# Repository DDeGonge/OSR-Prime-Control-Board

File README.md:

# OSR-Prime-Control-Board
It's like the OSR but more power more better

This repo is being deprecated. The board and arduino packages have been merged into the [OSR repo](https://github.com/DDeGonge/OSR-Control-Board)

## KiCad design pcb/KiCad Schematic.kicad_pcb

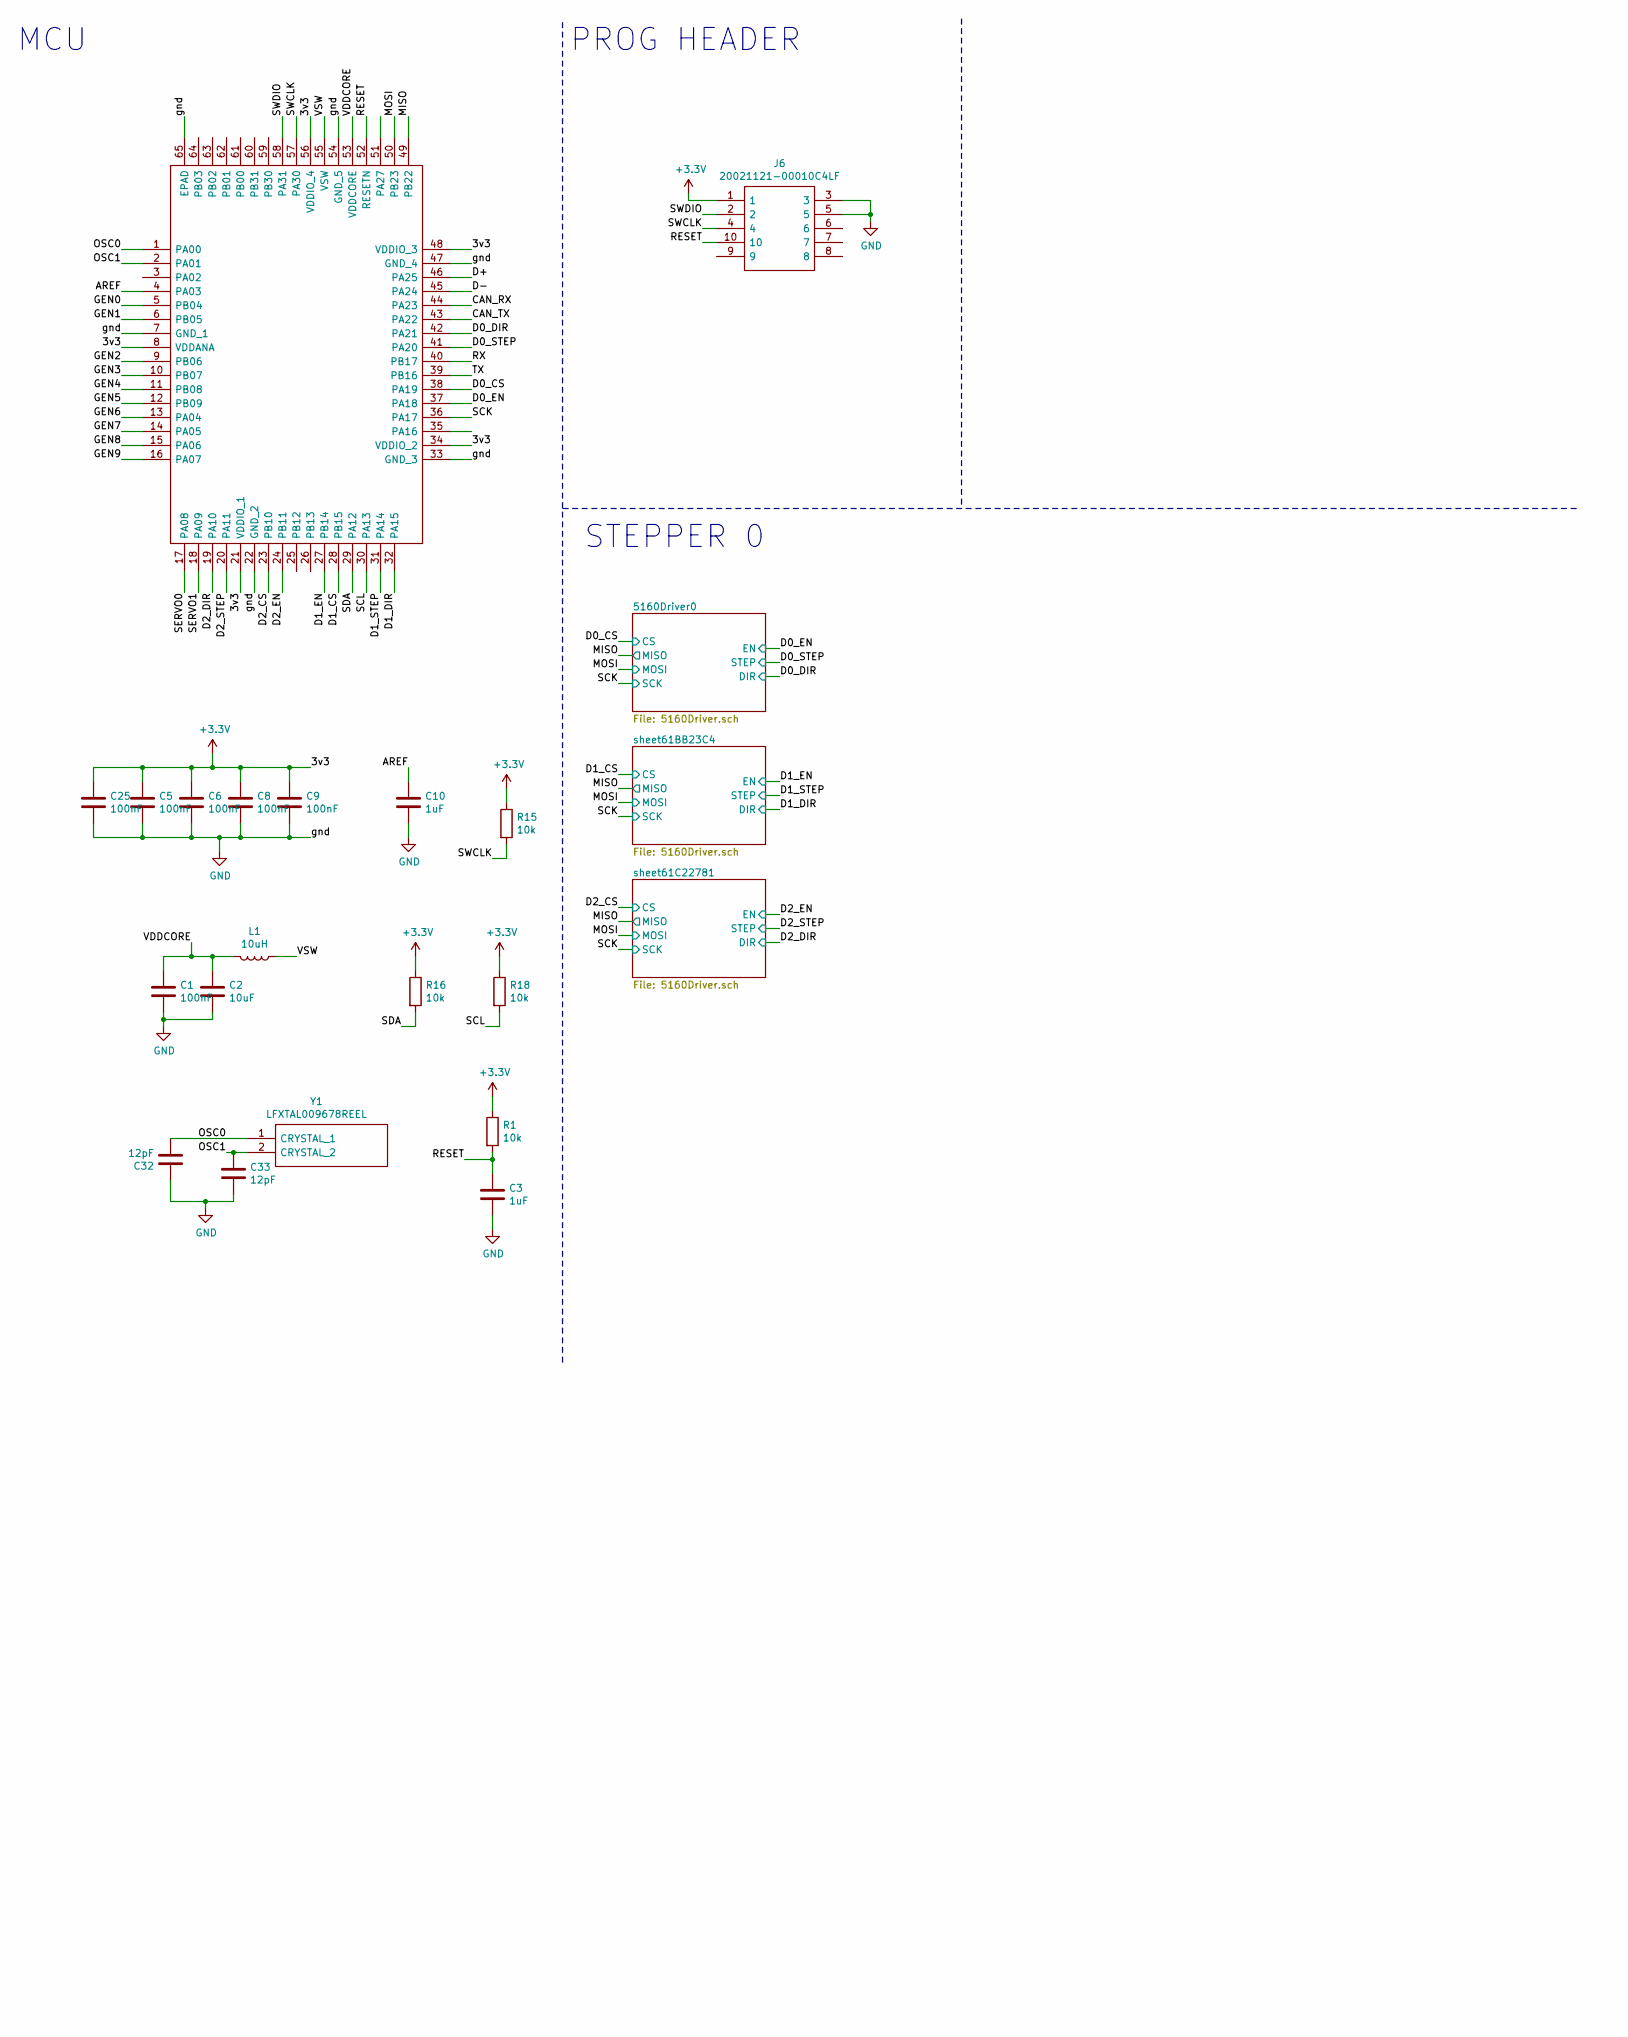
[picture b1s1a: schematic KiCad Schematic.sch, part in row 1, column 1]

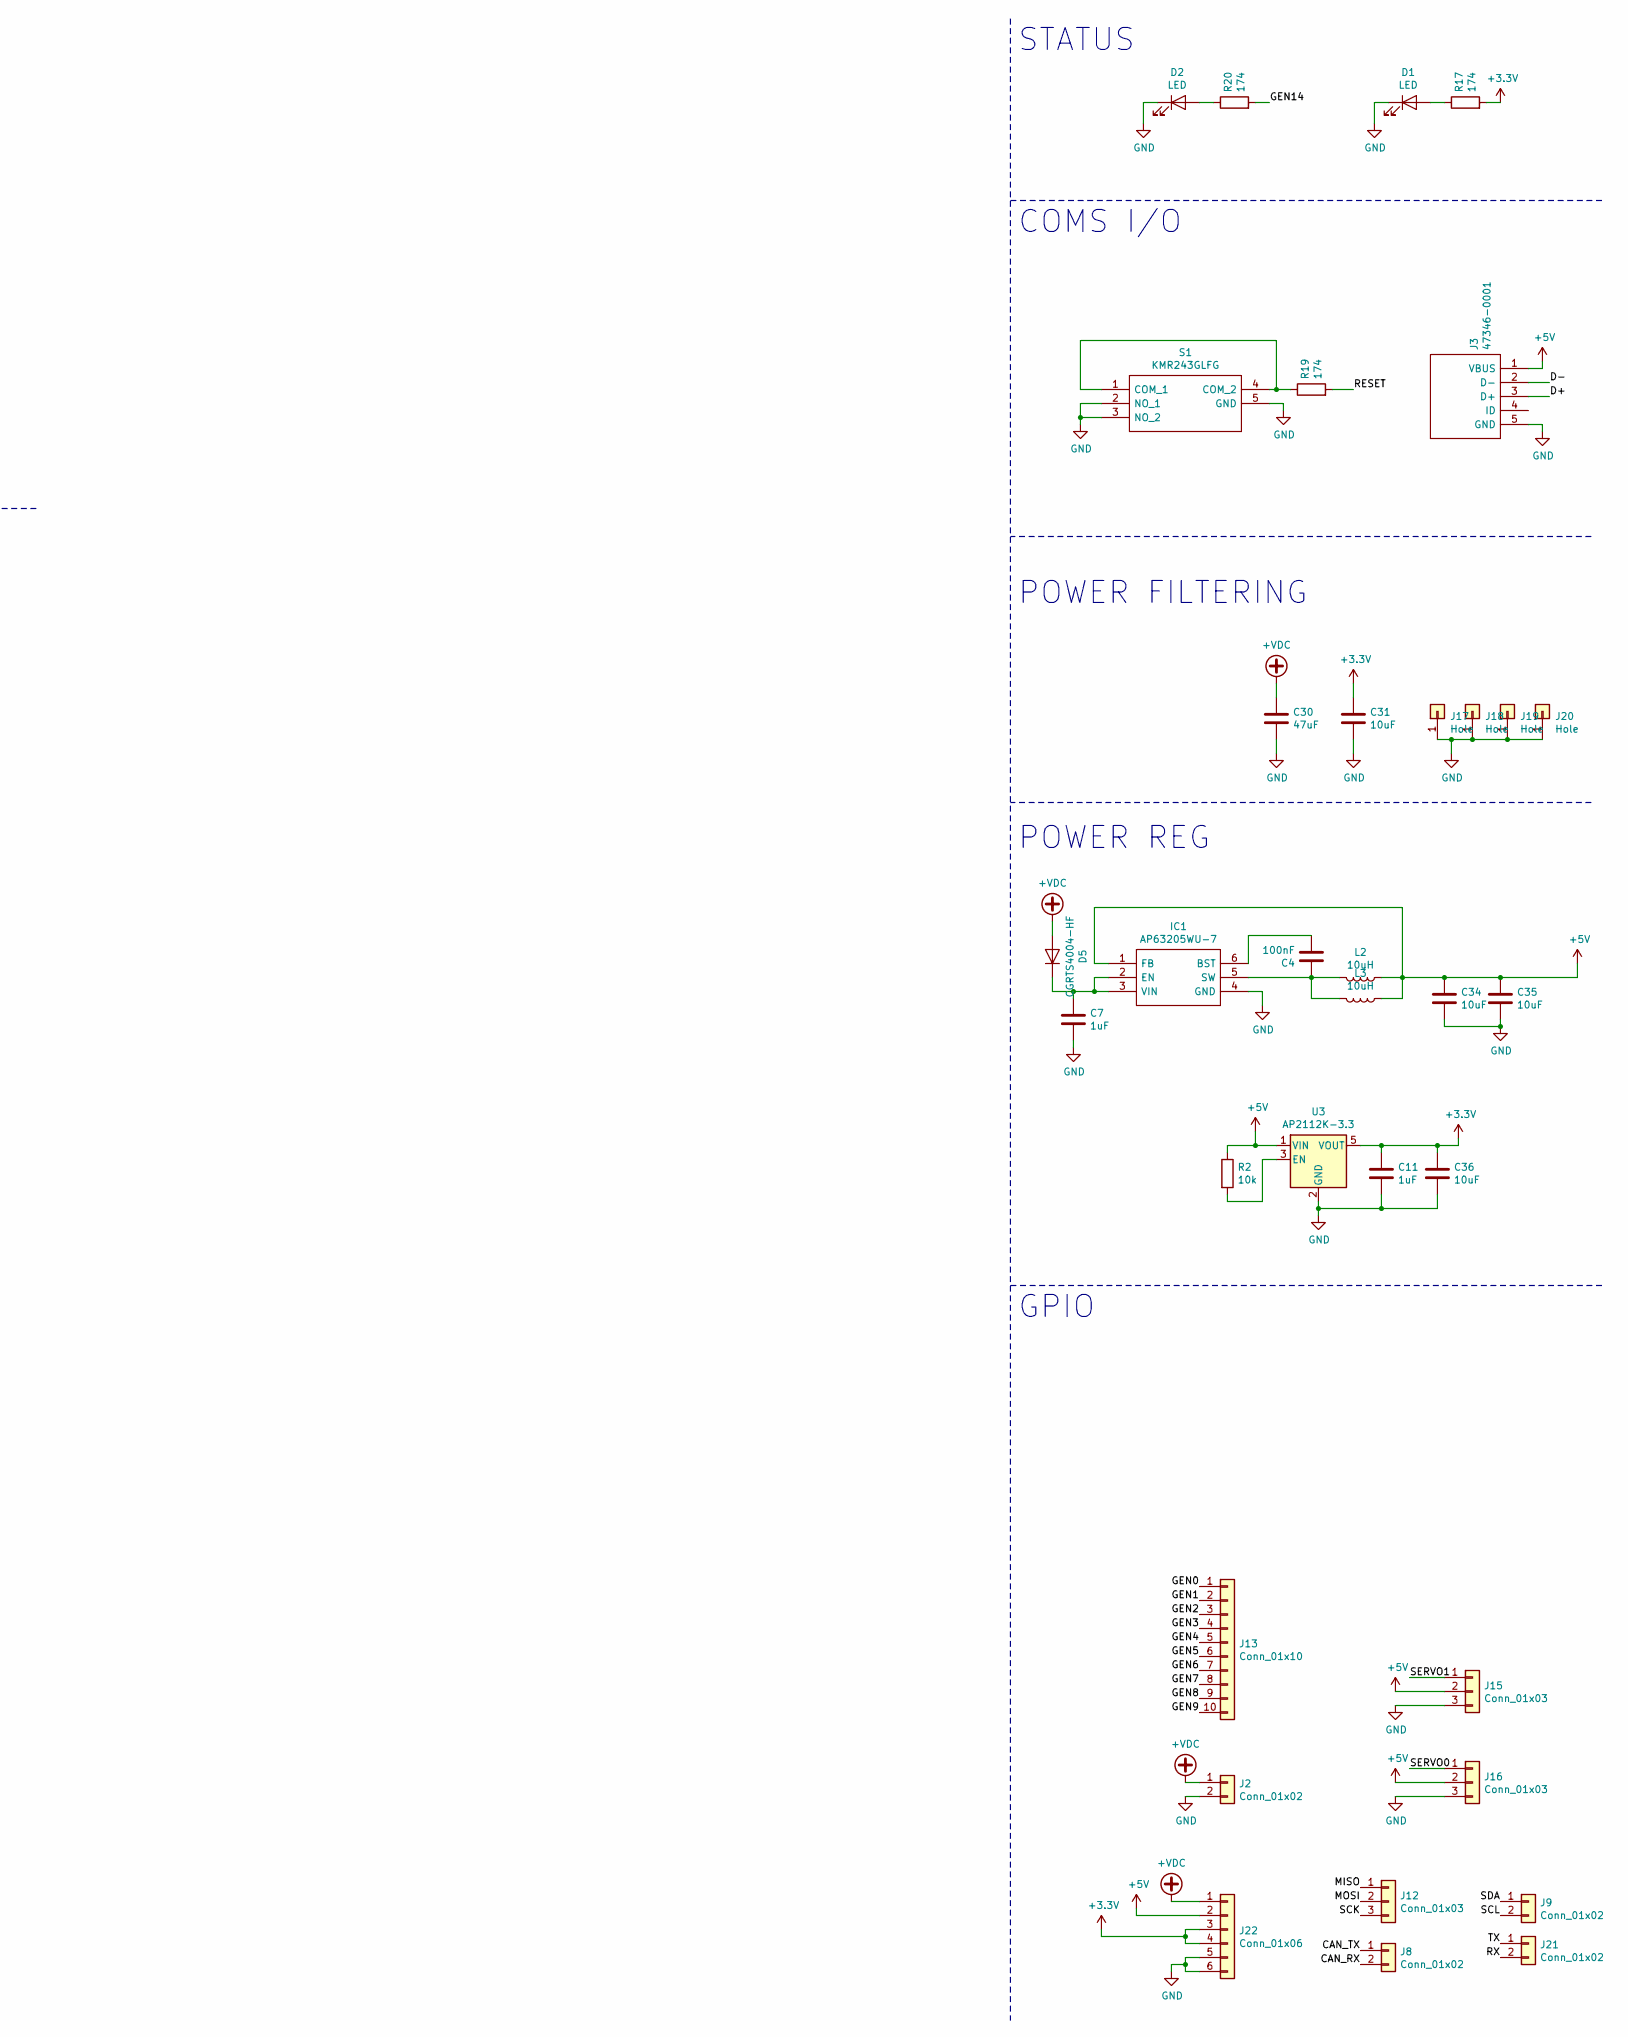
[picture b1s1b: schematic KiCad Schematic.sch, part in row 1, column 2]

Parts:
C1, C4, C5, C6, C8, C9, C25: 100nF; C_0603_1608Metric
C2, C31, C34, C35, C36: 10uF; C_0805_2012Metric
C3, C7, C10, C11: 1uF; C_0603_1608Metric
C30: 47uF; CP_Elec_6.3x7.7
C32, C33: 12pF; C_0603_1608Metric
D1, D2: LED; LED_0603_1608Metric
D5: CGRTS4004-HF; D_SOD-123F
IC1: AP63205WU-7; SOT95P280X100-6N; Mouser Part Number 621-AP63205WU-7
IC2: ATSAMD51J19A-MU; QFN-64-1EP_9x9mm_P0.5mm_EP6x6mm_ThermalVias; Mouser Part Number 556-ATSAMD51J19AMU
J2: Conn_01x02; BarrelJack_Wuerth_6941xx301002
J3: 47346-0001; Mouser Part Number 538-47346-0001
J6: 20021121-00010C4LF; 2002112100010C4LF; Mouser Part Number 649-202112100010C4LF
J8, J9, J21: Conn_01x02; PinHeader_1x02_P2.54mm_Vertical
J12, J15, J16: Conn_01x03; PinHeader_1x03_P2.54mm_Vertical
J13: Conn_01x10; PinHeader_1x10_P2.54mm_Vertical
J17, J18, J19, J20: Hole; MountingHole_2.7mm_M2.5_DIN965_Pad
J22: Conn_01x06; PinSocket_1x06_P2.54mm_Vertical
L1, L2, L3: 10uH; L_0805_2012Metric
R1, R2, R15, R16, R18: 10k; R_0603_1608Metric
R17, R19, R20: 174; R_0603_1608Metric
S1: KMR243GLFG; KMR421GULCLFS; Mouser Part Number 611-KMR243GLFG
U3: AP2112K-3.3; SOT-23-5
Y1: LFXTAL009678REEL; Mouser Part Number 449-LFXTAL009678REEL

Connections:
+3V3: C5.1, C6.1, C8.1, C9.1, C11.1, C25.1, C31.1, C36.1, IC2.8 (VDDANA), IC2.21 (VDDIO_1), IC2.34 (VDDIO_2), IC2.48 (VDDIO_3), IC2.56 (VDDIO_4), J6.1, J22.3, J22.4, R1.1, R15.1, R16.1, R17.2, R18.1, U3.5 (VOUT); also elsewhere on the board
+5V: C34.1, C35.1, IC1.1 (FB), J3.1 (VBUS), J15.2, J16.2, J22.2, L2.1, L3.1, R2.1, U3.1 (VIN); also elsewhere on the board
+VDC: C30.1, D5.2 (A), J2.1, J22.1; also elsewhere on the board
/AREF: C10.1, IC2.4 (PA03)
/CAN_RX: IC2.44 (PA23), J8.2
/CAN_TX: IC2.43 (PA22), J8.1
/D0_CS: IC2.38 (PA19); also elsewhere on the board
/D0_DIR: IC2.42 (PA21); also elsewhere on the board
/D0_EN: IC2.37 (PA18); also elsewhere on the board
/D0_STEP: IC2.41 (PA20); also elsewhere on the board
/D1_CS: IC2.28 (PB15); also elsewhere on the board
/D1_DIR: IC2.32 (PA15); also elsewhere on the board
/D1_EN: IC2.27 (PB14); also elsewhere on the board
/D1_STEP: IC2.31 (PA14); also elsewhere on the board
/D2_CS: IC2.23 (PB10); also elsewhere on the board
/D2_DIR: IC2.19 (PA10); also elsewhere on the board
/D2_EN: IC2.24 (PB11); also elsewhere on the board
/D2_STEP: IC2.20 (PA11); also elsewhere on the board
/D+: IC2.46 (PA25), J3.3 (D+)
/D-: IC2.45 (PA24), J3.2 (D-)
/GEN0: IC2.5 (PB04), J13.1
/GEN1: IC2.6 (PB05), J13.2
/GEN2: IC2.9 (PB06), J13.3
/GEN3: IC2.10 (PB07), J13.4
/GEN4: IC2.11 (PB08), J13.5
/GEN5: IC2.12 (PB09), J13.6
/GEN6: IC2.13 (PA04), J13.7
/GEN7: IC2.14 (PA05), J13.8
/GEN8: IC2.15 (PA06), J13.9
/GEN9: IC2.16 (PA07), J13.10
/GEN14: R20.2
/MISO: IC2.49 (PB22), J12.1; also elsewhere on the board
/MOSI: IC2.50 (PB23), J12.2; also elsewhere on the board
/OSC0: C32.2, IC2.1 (PA00), Y1.1 (CRYSTAL_1)
/OSC1: C33.1, IC2.2 (PA01), Y1.2 (CRYSTAL_2)
/RESET: C3.1, IC2.52 (RESETN), J6.10, R1.2, R19.2
/RX: IC2.40 (PB17), J21.2
/SCK: IC2.36 (PA17), J12.3; also elsewhere on the board
/SCL: IC2.30 (PA13), J9.2, R18.2
/SDA: IC2.29 (PA12), J9.1, R16.2
/SERVO0: IC2.17 (PA08), J16.1
/SERVO1: IC2.18 (PA09), J15.1
/SWCLK: IC2.57 (PA30), J6.4, R15.2
/SWDIO: IC2.58 (PA31), J6.2
/TX: IC2.39 (PB16), J21.1
/VDDCORE: C1.1, C2.1, IC2.53 (VDDCORE), L1.2
/VSW: IC2.55 (VSW), L1.1
GND: C1.2, C2.2, C3.2, C5.2, C6.2, C7.2, C8.2, C9.2, C10.2, C11.2, C25.2, C30.2, C31.2, C32.1, C33.2, C34.2, C35.2, C36.2, D1.1 (K), D2.1 (K), IC1.4 (GND), IC2.7 (GND_1), IC2.22 (GND_2), IC2.33 (GND_3), IC2.47 (GND_4), IC2.54 (GND_5), IC2.65 (EPAD), J2.2, J3.5 (GND), J6.3, J6.5, J15.3, J16.3, J17.1, J18.1, J19.1, J20.1, J22.5, J22.6, S1.2 (NO_1), S1.3 (NO_2), S1.5 (GND), U3.2 (GND); also elsewhere on the board
unnamed: C4.1, IC1.5 (SW), L2.2, L3.2
unnamed: C4.2, IC1.6 (BST)
unnamed: C7.1, D5.1 (K), IC1.2 (EN), IC1.3 (VIN)
unnamed: D1.2 (A), R17.1
unnamed: D2.2 (A), R20.1
unnamed: R2.2, U3.3 (EN)
unnamed: R19.1, S1.1 (COM_1), S1.4 (COM_2)

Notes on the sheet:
GPIO
POWER REG
POWER FILTERING
COMS I/O
STATUS
PROG HEADER
MCU
STEPPER 0

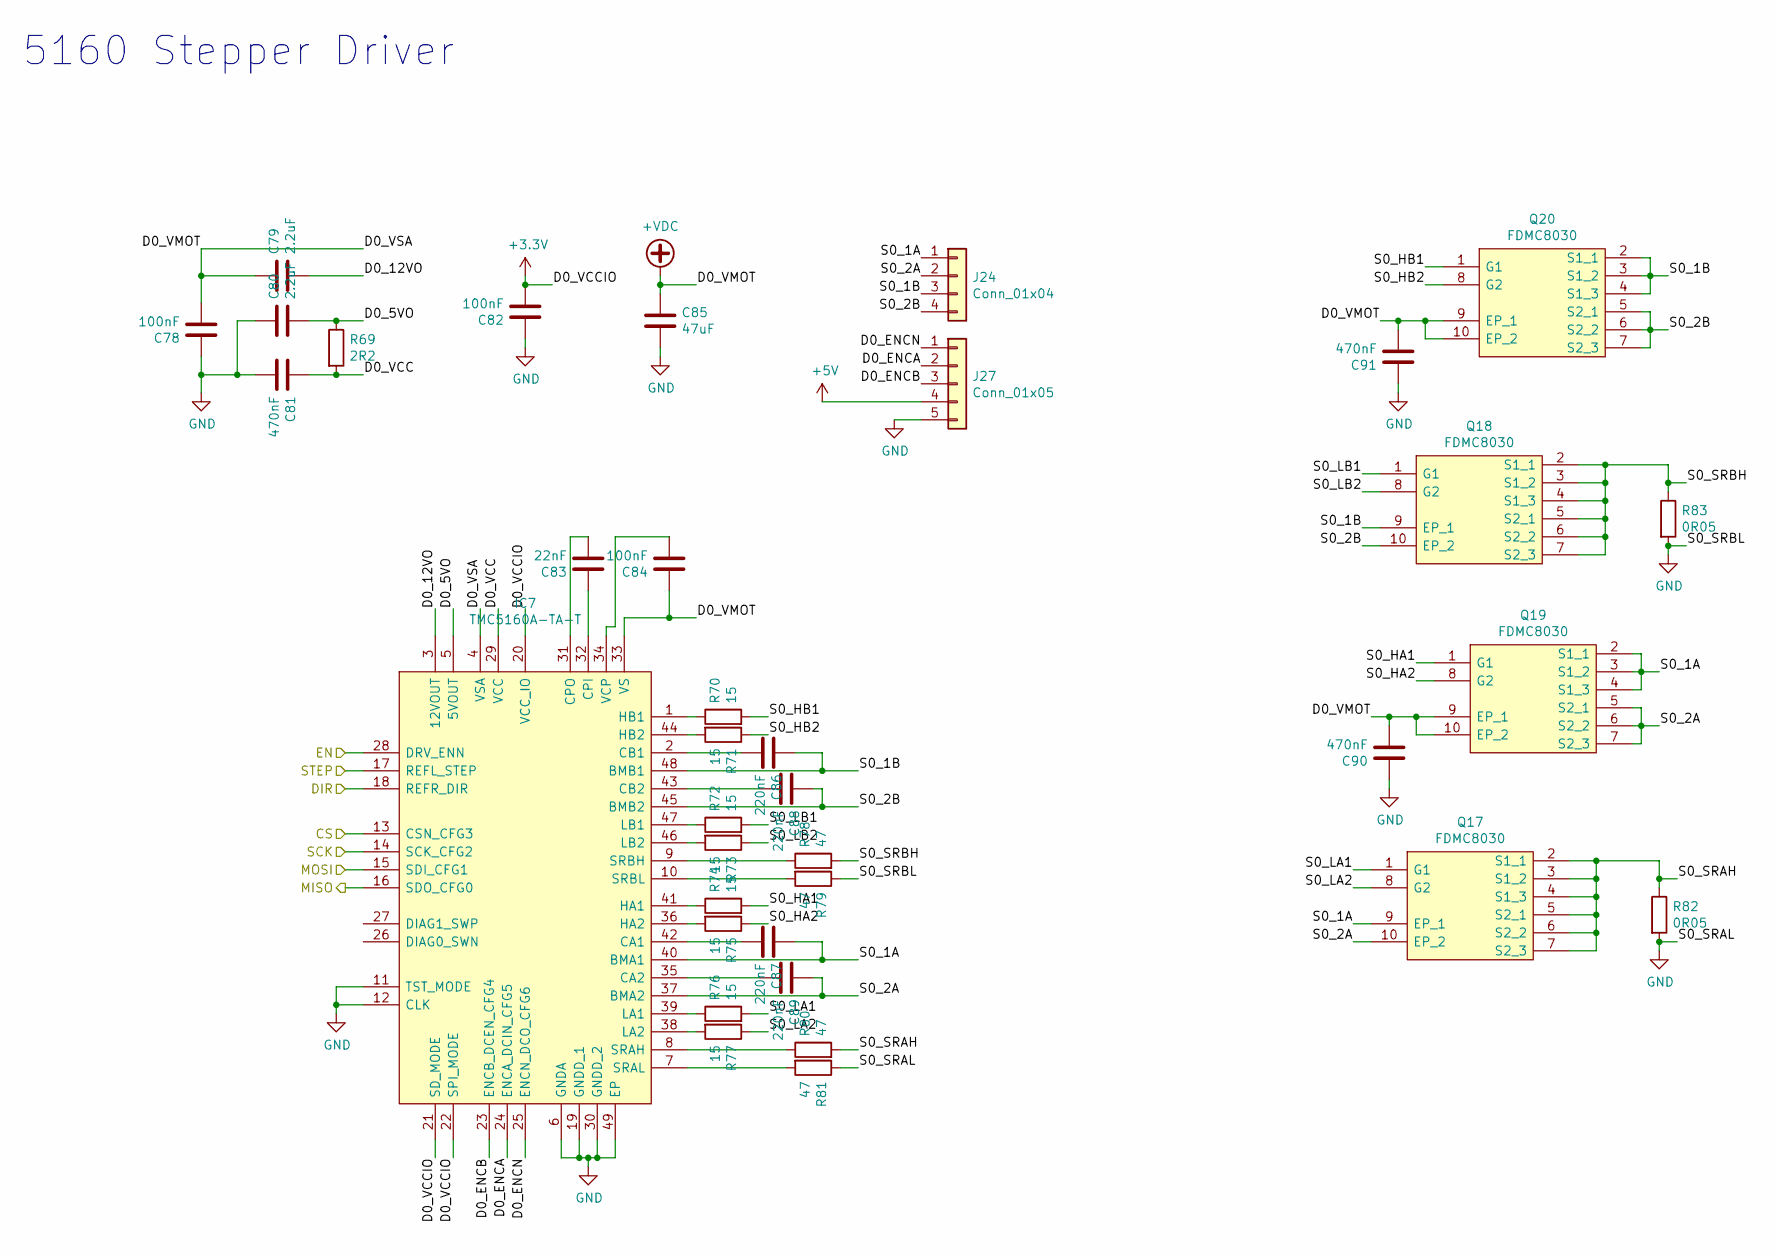
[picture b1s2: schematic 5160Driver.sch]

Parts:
C28, C39, C41: 100nF; C_0603_1608Metric
C29, C37: 2.2uF; C_1206_3216Metric
C38, C48, C54: 470nF; C_0603_1608Metric
C40: 22nF; C_0603_1608Metric
C43: 47uF; CP_Elec_6.3x7.7
C44, C45, C46, C47: 220nF; C_0603_1608Metric
IC4: TMC5160A-TA-T; QFP50P900X900X120-49N
J14: Conn_01x04; PinHeader_1x04_P2.54mm_Vertical
J25: Conn_01x05; PinHeader_1x05_P2.54mm_Vertical
Q5, Q6, Q7, Q8: FDMC8030; FDMC89521L; Mouser Part Number 512-FDMC8030
R24: 2R2; R_0603_1608Metric
R25, R26, R27, R28, R29, R30, R31, R32: 15; R_0603_1608Metric
R33, R34, R35, R36: 47; R_0603_1608Metric
R50, R51: 0R05; R_1206_3216Metric

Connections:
+3V3: C39.2, IC4.20 (VCC_IO), IC4.21 (SD_MODE), IC4.22 (SPI_MODE); also elsewhere on the board
+5V: J25.4; also elsewhere on the board
+VDC: C28.2, C29.1, C41.1, C43.1, C48.2, C54.2, IC4.4 (VSA), IC4.33 (VS), Q7.9 (EP_1), Q7.10 (EP_2), Q8.9 (EP_1), Q8.10 (EP_2); also elsewhere on the board
/5160Driver0/D0_5VO: C37.2, IC4.5 (5VOUT), R24.1
/5160Driver0/D0_12VO: C29.2, IC4.3 (12VOUT)
/5160Driver0/D0_ENCA: IC4.24 (ENCA_DCIN_CFG5), J25.2
/5160Driver0/D0_ENCB: IC4.23 (ENCB_DCEN_CFG4), J25.3
/5160Driver0/D0_ENCN: IC4.25 (ENCN_DCO_CFG6), J25.1
/5160Driver0/D0_VCC: C38.1, IC4.29 (VCC), R24.2
/5160Driver0/S0_1A: C45.1, IC4.40 (BMA1), J14.1, Q5.9 (EP_1), Q7.2 (S1_1), Q7.3 (S1_2), Q7.4 (S1_3)
/5160Driver0/S0_1B: C44.1, IC4.48 (BMB1), J14.3, Q6.9 (EP_1), Q8.2 (S1_1), Q8.3 (S1_2), Q8.4 (S1_3)
/5160Driver0/S0_2A: C47.1, IC4.37 (BMA2), J14.2, Q5.10 (EP_2), Q7.5 (S2_1), Q7.6 (S2_2), Q7.7 (S2_3)
/5160Driver0/S0_2B: C46.1, IC4.45 (BMB2), J14.4, Q6.10 (EP_2), Q8.5 (S2_1), Q8.6 (S2_2), Q8.7 (S2_3)
/5160Driver0/S0_HA1: Q7.1 (G1), R29.2
/5160Driver0/S0_HA2: Q7.8 (G2), R30.1
/5160Driver0/S0_HB1: Q8.1 (G1), R25.2
/5160Driver0/S0_HB2: Q8.8 (G2), R26.1
/5160Driver0/S0_LA1: Q5.1 (G1), R31.2
/5160Driver0/S0_LA2: Q5.8 (G2), R32.1
/5160Driver0/S0_LB1: Q6.1 (G1), R27.2
/5160Driver0/S0_LB2: Q6.8 (G2), R28.1
/5160Driver0/S0_SRAH: Q5.2 (S1_1), Q5.3 (S1_2), Q5.4 (S1_3), Q5.5 (S2_1), Q5.6 (S2_2), Q5.7 (S2_3), R35.2, R50.1
/5160Driver0/S0_SRBH: Q6.2 (S1_1), Q6.3 (S1_2), Q6.4 (S1_3), Q6.5 (S2_1), Q6.6 (S2_2), Q6.7 (S2_3), R33.2, R51.1
/D0_CS: IC4.13 (CSN_CFG3); also elsewhere on the board
/D0_DIR: IC4.18 (REFR_DIR); also elsewhere on the board
/D0_EN: IC4.28 (DRV_ENN); also elsewhere on the board
/D0_STEP: IC4.17 (REFL_STEP); also elsewhere on the board
/MISO: IC4.16 (SDO_CFG0); also elsewhere on the board
/MOSI: IC4.15 (SDI_CFG1); also elsewhere on the board
/SCK: IC4.14 (SCK_CFG2); also elsewhere on the board
GND: C28.1, C37.1, C38.2, C39.1, C43.2, C48.1, C54.1, IC4.6 (GNDA), IC4.11 (TST_MODE), IC4.12 (CLK), IC4.19 (GNDD_1), IC4.30 (GNDD_2), IC4.49 (EP), J25.5, R34.1, R36.1, R50.2, R51.2; also elsewhere on the board
unnamed: C40.1, IC4.32 (CPI)
unnamed: C40.2, IC4.31 (CPO)
unnamed: C41.2, IC4.34 (VCP)
unnamed: C44.2, IC4.2 (CB1)
unnamed: C45.2, IC4.42 (CA1)
unnamed: C46.2, IC4.43 (CB2)
unnamed: C47.2, IC4.35 (CA2)
unnamed: IC4.1 (HB1), R25.1
unnamed: IC4.7 (SRAL), R36.2
unnamed: IC4.8 (SRAH), R35.1
unnamed: IC4.9 (SRBH), R33.1
unnamed: IC4.10 (SRBL), R34.2
unnamed: IC4.36 (HA2), R30.2
unnamed: IC4.38 (LA2), R32.2
unnamed: IC4.39 (LA1), R31.1
unnamed: IC4.41 (HA1), R29.1
unnamed: IC4.44 (HB2), R26.2
unnamed: IC4.46 (LB2), R28.2
unnamed: IC4.47 (LB1), R27.1

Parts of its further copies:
C55, C68, C70, C78, C82, C84: 100nF; C_0603_1608Metric
C65, C66, C79, C80: 2.2uF; C_1206_3216Metric
C67, C76, C77, C81, C90, C91: 470nF; C_0603_1608Metric
C69, C83: 22nF; C_0603_1608Metric
C71, C85: 47uF; CP_Elec_6.3x7.7
C72, C73, C74, C75, C86, C87, C88, C89: 220nF; C_0603_1608Metric
IC6, IC7: TMC5160A-TA-T; QFP50P900X900X120-49N
J23, J24: Conn_01x04; PinHeader_1x04_P2.54mm_Vertical
J26, J27: Conn_01x05; PinHeader_1x05_P2.54mm_Vertical
Q13, Q14, Q15, Q16, Q17, Q18, Q19, Q20: FDMC8030; FDMC89521L; Mouser Part Number 512-FDMC8030
R54, R69: 2R2; R_0603_1608Metric
R55, R56, R57, R58, R59, R60, R61, R62, R70, R71, R72, R73, R74, R75, R76, R77: 15; R_0603_1608Metric
R63, R64, R65, R66, R78, R79, R80, R81: 47; R_0603_1608Metric
R67, R68, R82, R83: 0R05; R_1206_3216Metric

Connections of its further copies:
+3V3: C68.2, C82.2, IC6.20 (VCC_IO), IC6.21 (SD_MODE), IC6.22 (SPI_MODE), IC7.20 (VCC_IO), IC7.21 (SD_MODE), IC7.22 (SPI_MODE); also elsewhere on the board
+5V: J26.4, J27.4; also elsewhere on the board
+VDC: C55.2, C65.1, C70.1, C71.1, C76.2, C77.2, C78.2, C79.1, C84.1, C85.1, C90.2, C91.2, IC6.4 (VSA), IC6.33 (VS), IC7.4 (VSA), IC7.33 (VS), Q15.9 (EP_1), Q15.10 (EP_2), Q16.9 (EP_1), Q16.10 (EP_2), Q19.9 (EP_1), Q19.10 (EP_2), Q20.9 (EP_1), Q20.10 (EP_2); also elsewhere on the board
/D1_CS: IC6.13 (CSN_CFG3); also elsewhere on the board
/D1_DIR: IC6.18 (REFR_DIR); also elsewhere on the board
/D1_EN: IC6.28 (DRV_ENN); also elsewhere on the board
/D1_STEP: IC6.17 (REFL_STEP); also elsewhere on the board
/D2_CS: IC7.13 (CSN_CFG3); also elsewhere on the board
/D2_DIR: IC7.18 (REFR_DIR); also elsewhere on the board
/D2_EN: IC7.28 (DRV_ENN); also elsewhere on the board
/D2_STEP: IC7.17 (REFL_STEP); also elsewhere on the board
/MISO: IC6.16 (SDO_CFG0), IC7.16 (SDO_CFG0); also elsewhere on the board
/MOSI: IC6.15 (SDI_CFG1), IC7.15 (SDI_CFG1); also elsewhere on the board
/SCK: IC6.14 (SCK_CFG2), IC7.14 (SCK_CFG2); also elsewhere on the board
/sheet61BB23C4/D0_5VO: C66.2, IC6.5 (5VOUT), R54.1
/sheet61BB23C4/D0_12VO: C65.2, IC6.3 (12VOUT)
/sheet61BB23C4/D0_ENCA: IC6.24 (ENCA_DCIN_CFG5), J26.2
/sheet61BB23C4/D0_ENCB: IC6.23 (ENCB_DCEN_CFG4), J26.3
/sheet61BB23C4/D0_ENCN: IC6.25 (ENCN_DCO_CFG6), J26.1
/sheet61BB23C4/D0_VCC: C67.1, IC6.29 (VCC), R54.2
/sheet61BB23C4/S0_1A: C73.1, IC6.40 (BMA1), J23.1, Q13.9 (EP_1), Q15.2 (S1_1), Q15.3 (S1_2), Q15.4 (S1_3)
/sheet61BB23C4/S0_1B: C72.1, IC6.48 (BMB1), J23.3, Q14.9 (EP_1), Q16.2 (S1_1), Q16.3 (S1_2), Q16.4 (S1_3)
/sheet61BB23C4/S0_2A: C75.1, IC6.37 (BMA2), J23.2, Q13.10 (EP_2), Q15.5 (S2_1), Q15.6 (S2_2), Q15.7 (S2_3)
/sheet61BB23C4/S0_2B: C74.1, IC6.45 (BMB2), J23.4, Q14.10 (EP_2), Q16.5 (S2_1), Q16.6 (S2_2), Q16.7 (S2_3)
/sheet61BB23C4/S0_HA1: Q15.1 (G1), R59.2
/sheet61BB23C4/S0_HA2: Q15.8 (G2), R60.1
/sheet61BB23C4/S0_HB1: Q16.1 (G1), R55.2
/sheet61BB23C4/S0_HB2: Q16.8 (G2), R56.1
/sheet61BB23C4/S0_LA1: Q13.1 (G1), R61.2
/sheet61BB23C4/S0_LA2: Q13.8 (G2), R62.1
/sheet61BB23C4/S0_LB1: Q14.1 (G1), R57.2
/sheet61BB23C4/S0_LB2: Q14.8 (G2), R58.1
/sheet61BB23C4/S0_SRAH: Q13.2 (S1_1), Q13.3 (S1_2), Q13.4 (S1_3), Q13.5 (S2_1), Q13.6 (S2_2), Q13.7 (S2_3), R65.2, R67.1
/sheet61BB23C4/S0_SRBH: Q14.2 (S1_1), Q14.3 (S1_2), Q14.4 (S1_3), Q14.5 (S2_1), Q14.6 (S2_2), Q14.7 (S2_3), R63.2, R68.1
/sheet61C22781/D0_5VO: C80.2, IC7.5 (5VOUT), R69.1
/sheet61C22781/D0_12VO: C79.2, IC7.3 (12VOUT)
/sheet61C22781/D0_ENCA: IC7.24 (ENCA_DCIN_CFG5), J27.2
/sheet61C22781/D0_ENCB: IC7.23 (ENCB_DCEN_CFG4), J27.3
/sheet61C22781/D0_ENCN: IC7.25 (ENCN_DCO_CFG6), J27.1
/sheet61C22781/D0_VCC: C81.1, IC7.29 (VCC), R69.2
/sheet61C22781/S0_1A: C87.1, IC7.40 (BMA1), J24.1, Q17.9 (EP_1), Q19.2 (S1_1), Q19.3 (S1_2), Q19.4 (S1_3)
/sheet61C22781/S0_1B: C86.1, IC7.48 (BMB1), J24.3, Q18.9 (EP_1), Q20.2 (S1_1), Q20.3 (S1_2), Q20.4 (S1_3)
/sheet61C22781/S0_2A: C89.1, IC7.37 (BMA2), J24.2, Q17.10 (EP_2), Q19.5 (S2_1), Q19.6 (S2_2), Q19.7 (S2_3)
/sheet61C22781/S0_2B: C88.1, IC7.45 (BMB2), J24.4, Q18.10 (EP_2), Q20.5 (S2_1), Q20.6 (S2_2), Q20.7 (S2_3)
/sheet61C22781/S0_HA1: Q19.1 (G1), R74.2
/sheet61C22781/S0_HA2: Q19.8 (G2), R75.1
/sheet61C22781/S0_HB1: Q20.1 (G1), R70.2
/sheet61C22781/S0_HB2: Q20.8 (G2), R71.1
/sheet61C22781/S0_LA1: Q17.1 (G1), R76.2
/sheet61C22781/S0_LA2: Q17.8 (G2), R77.1
/sheet61C22781/S0_LB1: Q18.1 (G1), R72.2
/sheet61C22781/S0_LB2: Q18.8 (G2), R73.1
/sheet61C22781/S0_SRAH: Q17.2 (S1_1), Q17.3 (S1_2), Q17.4 (S1_3), Q17.5 (S2_1), Q17.6 (S2_2), Q17.7 (S2_3), R80.2, R82.1
/sheet61C22781/S0_SRBH: Q18.2 (S1_1), Q18.3 (S1_2), Q18.4 (S1_3), Q18.5 (S2_1), Q18.6 (S2_2), Q18.7 (S2_3), R78.2, R83.1
GND: C55.1, C66.1, C67.2, C68.1, C71.2, C76.1, C77.1, C78.1, C80.1, C81.2, C82.1, C85.2, C90.1, C91.1, IC6.6 (GNDA), IC6.11 (TST_MODE), IC6.12 (CLK), IC6.19 (GNDD_1), IC6.30 (GNDD_2), IC6.49 (EP), IC7.6 (GNDA), IC7.11 (TST_MODE), IC7.12 (CLK), IC7.19 (GNDD_1), IC7.30 (GNDD_2), IC7.49 (EP), J26.5, J27.5, R64.1, R66.1, R67.2, R68.2, R79.1, R81.1, R82.2, R83.2; also elsewhere on the board
unnamed: C69.1, IC6.32 (CPI)
unnamed: C69.2, IC6.31 (CPO)
unnamed: C70.2, IC6.34 (VCP)
unnamed: C72.2, IC6.2 (CB1)
unnamed: C73.2, IC6.42 (CA1)
unnamed: C74.2, IC6.43 (CB2)
unnamed: C75.2, IC6.35 (CA2)
unnamed: C83.1, IC7.32 (CPI)
unnamed: C83.2, IC7.31 (CPO)
unnamed: C84.2, IC7.34 (VCP)
unnamed: C86.2, IC7.2 (CB1)
unnamed: C87.2, IC7.42 (CA1)
unnamed: C88.2, IC7.43 (CB2)
unnamed: C89.2, IC7.35 (CA2)
unnamed: IC6.1 (HB1), R55.1
unnamed: IC6.7 (SRAL), R66.2
unnamed: IC6.8 (SRAH), R65.1
unnamed: IC6.9 (SRBH), R63.1
unnamed: IC6.10 (SRBL), R64.2
unnamed: IC6.36 (HA2), R60.2
unnamed: IC6.38 (LA2), R62.2
unnamed: IC6.39 (LA1), R61.1
unnamed: IC6.41 (HA1), R59.1
unnamed: IC6.44 (HB2), R56.2
unnamed: IC6.46 (LB2), R58.2
unnamed: IC6.47 (LB1), R57.1
unnamed: IC7.1 (HB1), R70.1
unnamed: IC7.7 (SRAL), R81.2
unnamed: IC7.8 (SRAH), R80.1
unnamed: IC7.9 (SRBH), R78.1
unnamed: IC7.10 (SRBL), R79.2
unnamed: IC7.36 (HA2), R75.2
unnamed: IC7.38 (LA2), R77.2
unnamed: IC7.39 (LA1), R76.1
unnamed: IC7.41 (HA1), R74.1
unnamed: IC7.44 (HB2), R71.2
unnamed: IC7.46 (LB2), R73.2
unnamed: IC7.47 (LB1), R72.1

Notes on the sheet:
5160 Stepper Driver

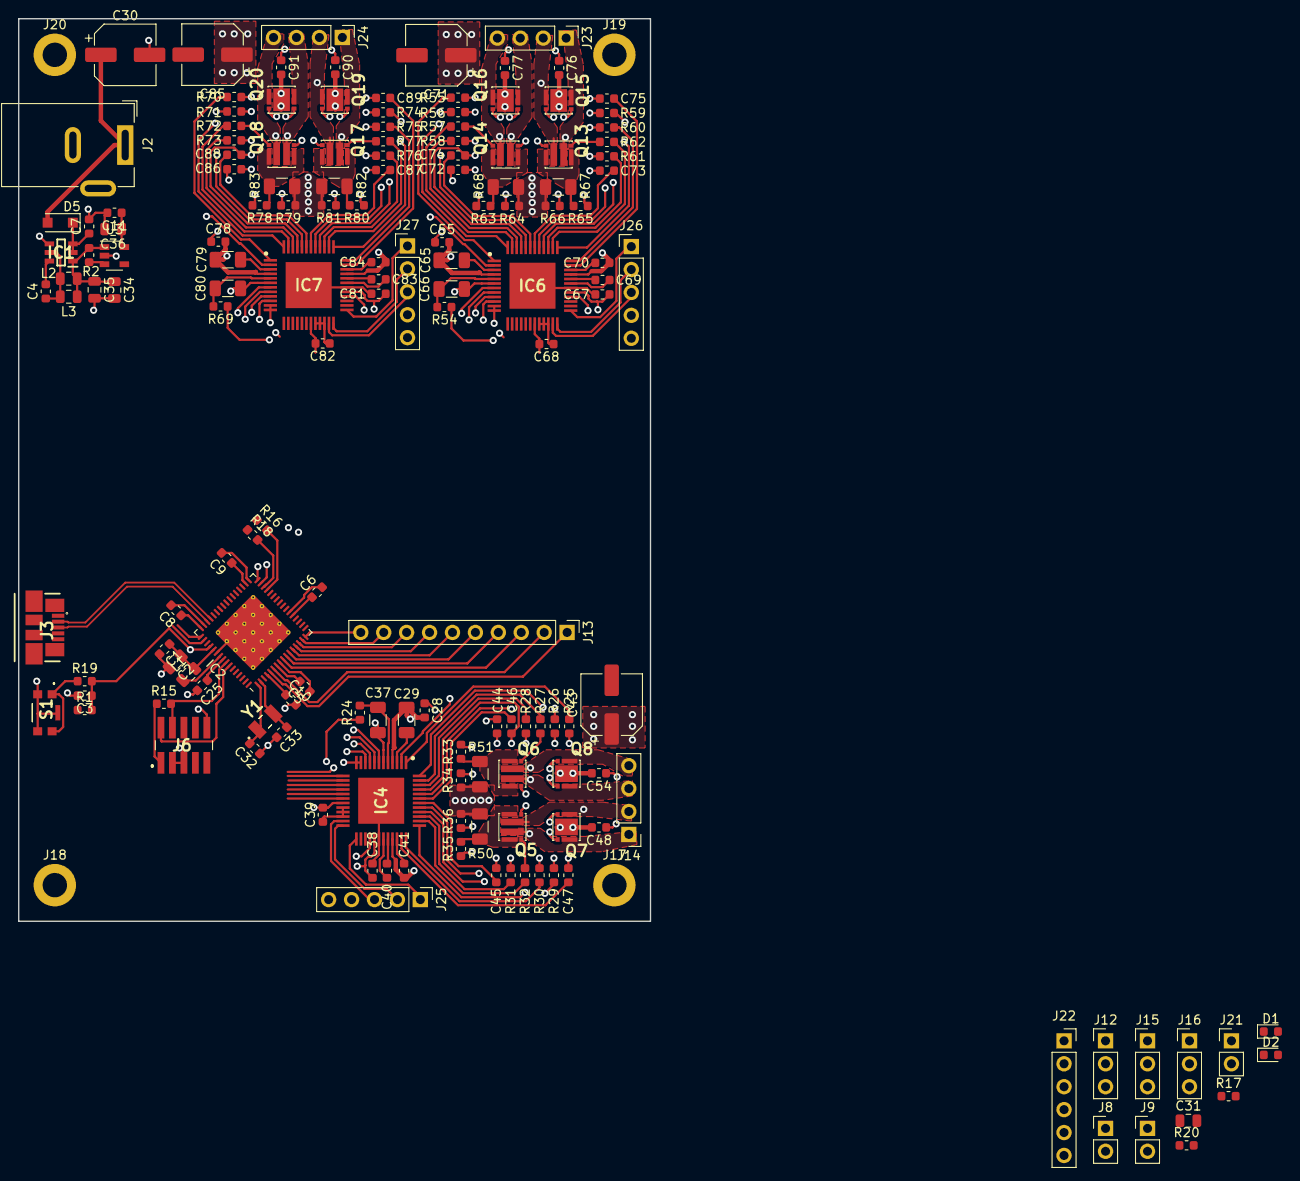
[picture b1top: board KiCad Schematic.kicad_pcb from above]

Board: 4 copper layers, 70.0 x 100.0 mm, 161 parts (0 on the bottom side), 171 nets.

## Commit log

2021-04-06 initial push
2021-06-20 final 1.0 stuff and first pass arduino library
2021-06-20 fix git url...is main the new master???
2021-06-20 bugfix bump
2021-06-21 url fix
2021-06-21 real url fix this time i swear
2021-06-21 arduino package bugfix attempt
2021-06-21 merged into osr repo
